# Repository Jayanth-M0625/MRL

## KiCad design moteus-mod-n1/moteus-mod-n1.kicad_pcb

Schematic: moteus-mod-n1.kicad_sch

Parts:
A1: PAD16AWG_TERM; 16AWG_TERMcustom
B1: PAD16AWG_TERM; 16AWG_TERMcustom
C1, C3, C6, C10, C33, C46, C47, C53, C64, C70, C72: 0.1uF; C0402; MPN MF-CAP-0402-0.1uF
C2: 0.47uF 100V; C0805; MPN 08051C474KAT2A
C4, C7: 0.1uF 100V; C0603; MPN GCJ188R72A104KA01D
C5, C8: 1uF; C0603; MPN C1608X7R1E105K080AE
C9: DNP; C0402
C11, C16, C21, C57: 1uF; C0402; MPN MF-CAP-0402-1uF
C12: 1uF 100V; C0805; MPN GCM21BC72A105KE36L
C13: 1uF; C0603; MPN MF-CAP-0603-1uF
C14, C17, C19: 0.1uF 100V; C1206; MPN 12061C104KAT2A
C15: 22uF; C1206; MPN GRM31CR71A226KE15L
C18: PAD16AWG_TERM; 16AWG_TERMcustom
C20: 22uF; C1206; MPN CL31B226KPHNNNE
C22, C23, C24, C25, C26, C27, C28, C29, C30, C31, C34, C35, C36, C37, C38, C39, C40, C41, C43, C44, C45, C48, C49, C50, C54, C55, C56, C58, C59, C60, C61, C62, C63, C65, C66, C67, C69, C71, C76, C77, C78, C79, C80, C81, C82, C83, C84, C85: 4.7uF 100V; C1206_NOBORDER; MPN GRJ31CC72A475KE01K
C32: 0.01uF; C0402; MPN MF-CAP-0402-0.01uF
C42, C51: 4.7uF 100V; C1206; MPN GRJ31CC72A475KE01K
C52: 4.7uF; C0603; MPN CL10A475KP8NNNC
C68: 10uF; C1206; MPN MF-CAP-1206-10uF
C73, C74, C75: 1000pF; C0402; MPN MF-CAP-0402-1nF
CAN1, CAN2, CAN3: 1X3
D1, D2, D3, D4, D5, D6, D7, D8, D9: BAT41KFILM; SODFL1608X70N; MPN BAT41KFILM
D10: MF-LED-0603-RED; LED0603
D11: MF-LED-0603-RED; LED0603; MPN MF-LED-0603-GREEN
D12: DIODE-DO214AA; DO214AA; MPN SMBJ51D-M3/I
D13, D14: PAD24AWG_PAD; 24AWG_PAD
DAC1: PAD24AWG_PAD; 24AWG_PAD
DG1: PAD24AWG_PAD; 24AWG_PAD
L1: SRN4018-220M; IND_BOURNS_SRN4018; MANUFACTURER_PART_NUMBER 74404042470
L2: 74479887222A; IND_1008_WE-PMI_WRE; MPN 74479887222A
M1, M2, M3: MOUNT; M2.5MOUNT
Q1, Q3, Q5: TPH1R204PL_VIAS; SOP_ADVANCE_8_VIAS; MPN TPH2R408QM,L1Q
Q2, Q4, Q6: TPH1R204PLSOP_ADVANCE_8; SOP_ADVANCE_8; MPN TPH2R408QM,L1Q
R1, R2: 2k; R0402; MPN MF-RES-0402-2K
R3, R8, R13: 0; R0402; MPN MF-RES-0402-0
R4, R17: DNP; R0402
R5: DNP; R0805
R6, R7, R10, R11, R12: 7.5; R0402; MPN RC0402FR-077R5L
R9: 7.5; R0805; MPN RC0805FR-077R5L
R14, R16: 100k 1%; R0402; MPN RC0402FR-07100KL
R15: 4.7k 1%; R0402; MPN RC0402FR-074K7L
R18, R21: 560; R0402; MPN MF-RES-0402-560
R19: 47k NTC; R0402; MPN NCP15WB473F03RC
R20, R22: 10k 1%; R0402; MPN RC0402FR-0710KL
R23, R24, R25: 22; R0402; MPN MF-RES-0402-22
RA1: 0.5mOhm 1% 2W; M1206; MPN HCS1206FTL500
RB1: 0.5mOhm 1% 2W; M1206; MPN HCS1206FTL500
RC1: 0.5mOhm 1% 2W; M1206; MPN HCS1206FTL500
SH1: SHORTMEDIUM; SHORT_TOP-MEDIUM
SH2, SH3, SH4: SHORTT5; SHORT_TOP-50
SWD1: JST-ZH6; JST_S6B-ZR-SM4A-TF(LF)(SN); MPN S6B-ZR-SM4A-TF(LF)(SN)
TEMP1: 1X2
U1: TCAN1042HGV; SOIC8; MPN TCAN1057AEVDRQ1
U2: AS5147; TSSOP14; MPN AS5047P-ATSM
U3: DRV8353S; WQFN-40; MPN DRV8353FSRTAR
U4: MAX15062AATA+T; 21-0487A_MXM; MANUFACTURER_PART_NUMBER MAX15062BATA+T
U5: ADP5301ACBZ-4-R7; BGA9C50P3X3_165X187X66; MPN ADP5301ACBZ-4-R7
U6: STM32G474CEU6; QFN50P700X700X60-49N; MPN STM32G474CEU6
VN1: PAD16AWG_TERM; 16AWG_TERMcustom
VP1: PAD16AWG_TERM; 16AWG_TERMcustom

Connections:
+3V3: C3.P$1, C6.P$2, C10.P$1, C20.P$1, C21.P$1, C46.P$1, C47.P$1, C52.P$1, C57.P$1, C64.P$1, C68.P$2, C70.P$1, D14.P$1, L2.1, R1.P$1, R2.P$1, R3.P$2, R16.P$2, R18.P$1, R19.P$1, R21.P$1, SWD1.6, TEMP1.1, U1.5 (VIO), U2.12 (VDD3V), U3.24 (VREF), U5.C2 (FB), U6.1 (VBAT), U6.20 (VREF+), U6.21 (VDDA), U6.23 (VDD_1), U6.35 (VDD_2), U6.48 (VDD_3)
+5V: C1.P$1, C15.P$1, C16.P$1, D13.P$1, L1.1, R13.P$2, U1.3 (VCC), U4.4 (FB/VOUT), U5.A2 (PVIN), U5.A3 (EN)
/AS5047_CS: U2.1 (CS/), U6.19 (PB2)
/AUX1_A: U2.2 (CLK), U6.13 (PA5), U6.27 (PB14)
/AUX1_B: U2.3 (MISO), U6.42 (PB4)
/AUX1_C: U2.4 (MOSI), U6.15 (PA7)
/CAN_N: CAN1.2, CAN2.2, CAN3.2, R5.P$2, U1.6 (CANL)
/CAN_P: CAN1.1, CAN2.1, CAN3.1, R5.P$1, U1.7 (CANH)
/CAN_RX: U1.4 (RXD), U6.43 (PB5)
/CAN_TX: U1.1 (TXD), U6.44 (PB6)
/CUR1: R23.P$1, U3.23 (SOA)
/CUR2: R24.P$1, U3.22 (SOB)
/CUR3: R25.P$1, U3.21 (SOC)
/DAC: DAC1.P$1, R16.P$1, R17.P$2, U6.12 (PA4)
/DRV8323_CS: U3.30 (CS), U6.17 (PB0)
/DRV8323_MISO: R1.P$2, U3.27 (MISO), U6.40 (PC11)
/DRV8323_MOSI: U3.28 (MOSI), U6.2 (PC13)
/DRV8323_SCLK: U3.29 (SCLK), U6.39 (PC10)
/FCUR1: C73.P$1, R23.P$2, U6.11 (PA3)
/FCUR2: C74.P$1, R24.P$2, U6.14 (PA6)
/FCUR3: C75.P$1, R25.P$2, U6.18 (PB1)
/GHA: D2.1 (K), R7.P$1, U3.6 (GHA)
/GHA_D: D2.2 (A), Q1.4 (G), R7.P$2
/GHB: D5.1 (K), R10.P$1, U3.15 (GHB)
/GHB_D: D5.2 (A), Q3.4 (G), R10.P$2
/GHC: D7.1 (K), R12.P$1, U3.16 (GHC)
/GHC_D: D7.2 (A), Q5.4 (G), R12.P$2
/GLA: D1.1 (K), R6.P$1, U3.8 (GLA)
/GLA_D: D1.2 (A), D3.1 (K), Q2.4 (G), R6.P$2
/GLB: D4.1 (K), R9.P$1, U3.13 (GLB)
/GLB_D: D4.2 (A), D6.1 (K), Q4.4 (G), R9.P$2
/GLC: D8.1 (K), R11.P$1, U3.18 (GLC)
/GLC_D: D8.2 (A), D9.1 (K), Q6.4 (G), R11.P$2
/LED1: D10.CATHODE, U6.28 (PB15)
/LED2: D11.CATHODE, U6.29 (PC6)
/MOTOR1: U3.32 (INHA), U6.8 (PA0)
/MOTOR2: U3.34 (INHB), U6.9 (PA1)
/MOTOR3: U3.36 (INHC), U6.10 (PA2)
/MOTOR_ENABLE: U3.31 (ENABLE), U6.3 (PC14-OSC32_IN)
/MOTOR_FAULT: R2.P$2, U3.26 (FAULT), U6.26 (PB13)
/MOTOR_HIZ: U3.33 (INLA), U3.35 (INLB), U3.37 (INLC), U6.4 (PC15-OSC32_OUT)
/NRST: C33.P$1, SWD1.2, U6.7 (PG10-NRST)
/SHA: A1.1, A1.2, A1.3, A1.4, A1.5, A1.6, A1.7, A1.8, A1.9, A1.10, A1.11, A1.12, A1.13, Q1.1 (S), Q1.2 (S), Q1.3 (S), Q2.5 (D), Q2.6 (D), Q2.7 (D), Q2.8 (D), Q2.PAD (D), U3.7 (SHA)
/SHB: B1.1, B1.2, B1.3, B1.4, B1.5, B1.6, B1.7, B1.8, B1.9, B1.10, B1.11, B1.12, B1.13, Q3.1 (S), Q3.2 (S), Q3.3 (S), Q4.5 (D), Q4.6 (D), Q4.7 (D), Q4.8 (D), Q4.PAD (D), U3.14 (SHB)
/SHC: C18.1, C18.2, C18.3, C18.4, C18.5, C18.6, C18.7, C18.8, C18.9, C18.10, C18.11, C18.12, C18.13, Q5.1 (S), Q5.2 (S), Q5.3 (S), Q6.5 (D), Q6.6 (D), Q6.7 (D), Q6.8 (D), Q6.PAD (D), U3.17 (SHC)
/SWCLK: SWD1.5, U6.37 (PA14)
/SWDIO: SWD1.3, U6.36 (PA13)
/SXA_N: SH2.1, U3.10 (SNA)
/SXA_P: C14.P$2, Q2.1 (S), Q2.2 (S), Q2.3 (S), RA1.2, U3.9 (SPA)
/SXB_N: SH3.1, U3.11 (SNB)
/SXB_P: C17.P$2, Q4.1 (S), Q4.2 (S), Q4.3 (S), RB1.2, U3.12 (SPB)
/SXC_N: SH4.1, U3.20 (SNC)
/SXC_P: C19.P$2, Q6.1 (S), Q6.2 (S), Q6.3 (S), RC1.2, U3.19 (SPC)
/VBAT_SENSE: C32.P$1, R14.P$1, R15.P$2, U6.31 (PA9)
/VSW: L1.2, U4.8 (LX)
/VTEMP_FET: C53.P$1, R19.P$2, R20.P$1, U6.25 (PB12)
/VTEMP_MOT: C72.P$1, R22.P$1, TEMP1.2, U6.30 (PA8)
unnamed: C9.P$1, M3.P$1, R4.P$1
unnamed: D10.ANODE, R18.P$2
unnamed: D11.ANODE, R21.P$2
unnamed: R3.P$1, U2.11 (VDD5V)
unnamed: C7.P$1, U3.2 (CPH)
unnamed: C7.P$2, U3.1 (CPL)
unnamed: C11.P$2, U3.38 (DVDD)
unnamed: C5.P$2, U3.5 (VCP)
unnamed: C8.P$2, U3.40 (VGLS)
unnamed: R8.P$2, U4.5 (MODE)
unnamed: C13.P$1, U4.3 (VCC)
unnamed: L2.2, U5.A1 (SW)
unnamed: R13.P$1, U5.B3 (SYNC/_MODE)
V+: C2.P$1, C4.P$1, C5.P$1, C12.P$1, C14.P$1, C17.P$1, C19.P$1, C22.P$1, C23.P$1, C24.P$1, C25.P$1, C26.P$1, C27.P$1, C28.P$1, C29.P$1, C30.P$1, C31.P$1, C34.P$1, C35.P$1, C36.P$1, C37.P$1, C38.P$1, C39.P$1, C40.P$1, C41.P$1, C42.P$1, C43.P$1, C44.P$1, C45.P$1, C48.P$1, C49.P$1, C50.P$1, C51.P$1, C54.P$1, C55.P$1, C56.P$1, C58.P$1, C59.P$1, C60.P$1, C61.P$1, C62.P$1, C63.P$1, C65.P$1, C66.P$1, C67.P$1, C69.P$1, C71.P$1, C76.P$1, C77.P$1, C78.P$1, C79.P$1, C80.P$1, C81.P$1, C82.P$1, C83.P$1, C84.P$1, C85.P$1, D12.C, Q1.5 (D), Q1.6 (D), Q1.7 (D), Q1.8 (D), Q1.PAD (D), Q3.5 (D), Q3.6 (D), Q3.7 (D), Q3.8 (D), Q3.PAD (D), Q5.5 (D), Q5.6 (D), Q5.7 (D), Q5.8 (D), Q5.PAD (D), R14.P$2, U3.3 (VM), U3.4 (VDRAIN), U4.1 (VIN), U4.2 (EN/UVLO), VP1.1, VP1.2, VP1.3, VP1.4, VP1.5, VP1.6, VP1.7, VP1.8, VP1.9, VP1.10, VP1.11, VP1.12, VP1.13

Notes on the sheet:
check component placement
POWER INPUT AND MOUNTING
CAN_L = CAN_N
OPTIONAL 120 TERMINATION RESISTOR
Need to connect either PA5 or PB14. Decide which one
BULK DC CAPS
MICROCONTROLLER
CAN_H = CAN_P
POWER STAGE
GATE DRIVER
Added 10 more DC Caps
NTC: Temperature sensing - keep near MOSFETs
Rotary encoder
This is where GND and V- are shorted
check how to connect this
CAN / ENCODER
check placement
This stage converts V+ into 5V and 3.3V
DEBUG
EXTERNAL CONNECTORS
PCB rev divider HI / LO r1.1/r1.2 - open / 100k r1.3 - 100k / open
REGULATORS
SENSE / LED

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
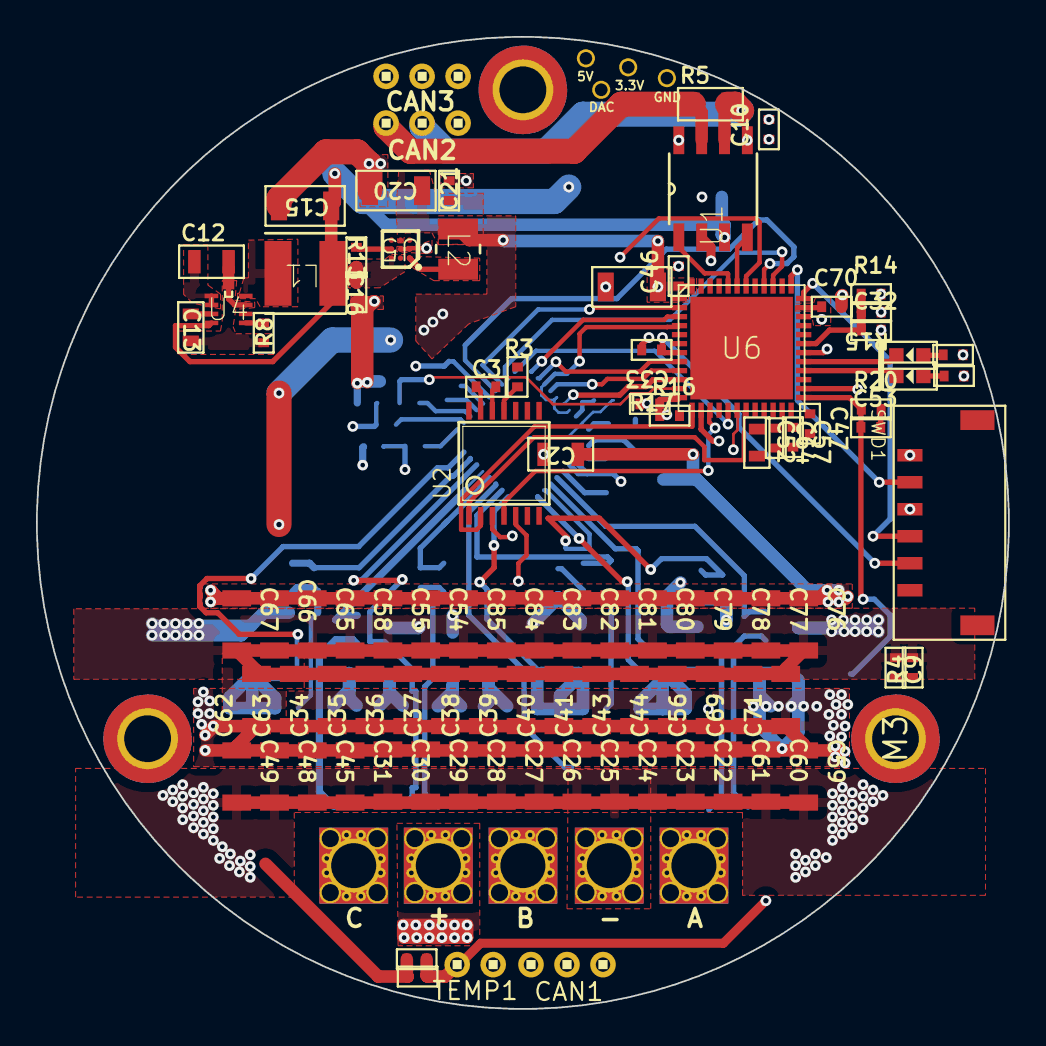
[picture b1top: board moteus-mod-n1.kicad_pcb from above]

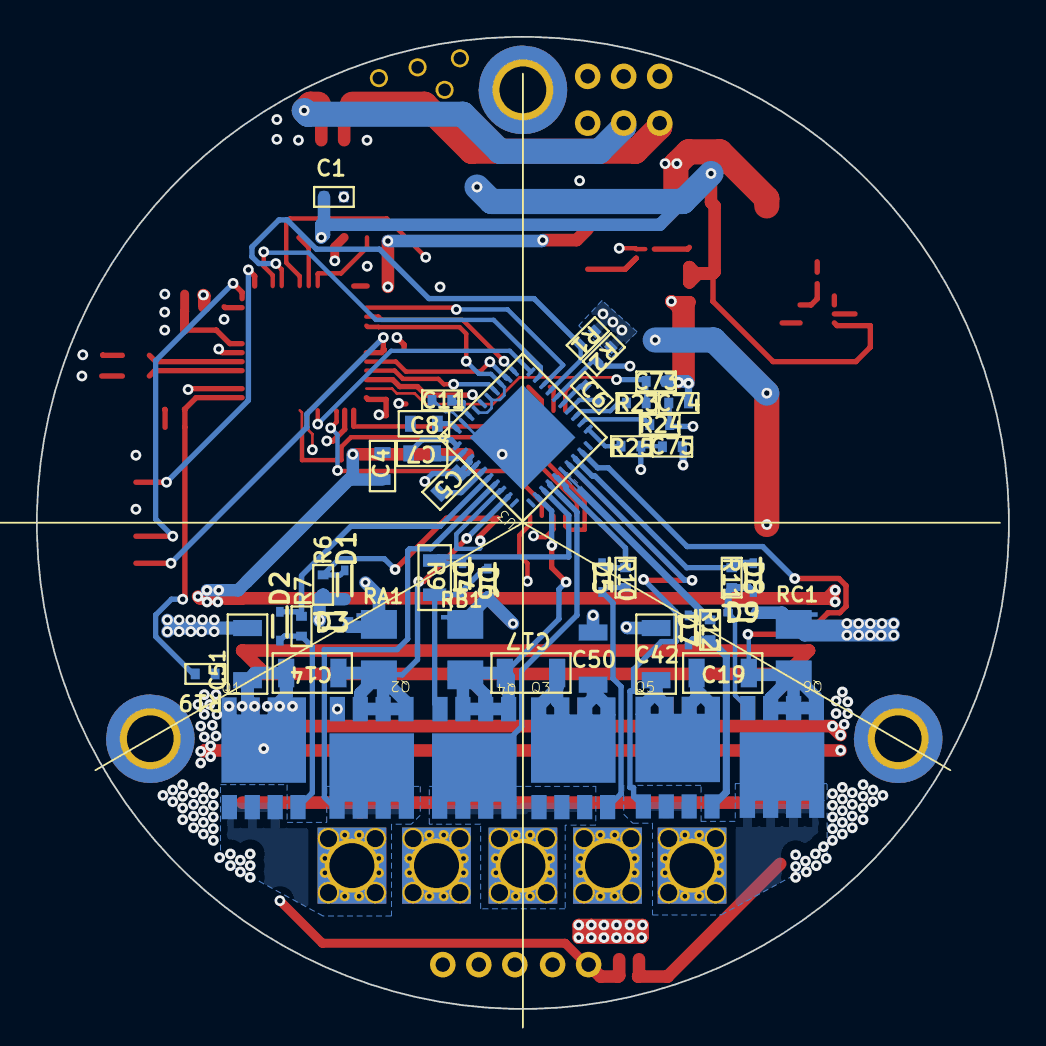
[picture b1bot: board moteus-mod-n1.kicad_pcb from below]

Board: 4 copper layers, 54.0 x 54.0 mm, 158 parts (50 on the bottom side), 73 nets.

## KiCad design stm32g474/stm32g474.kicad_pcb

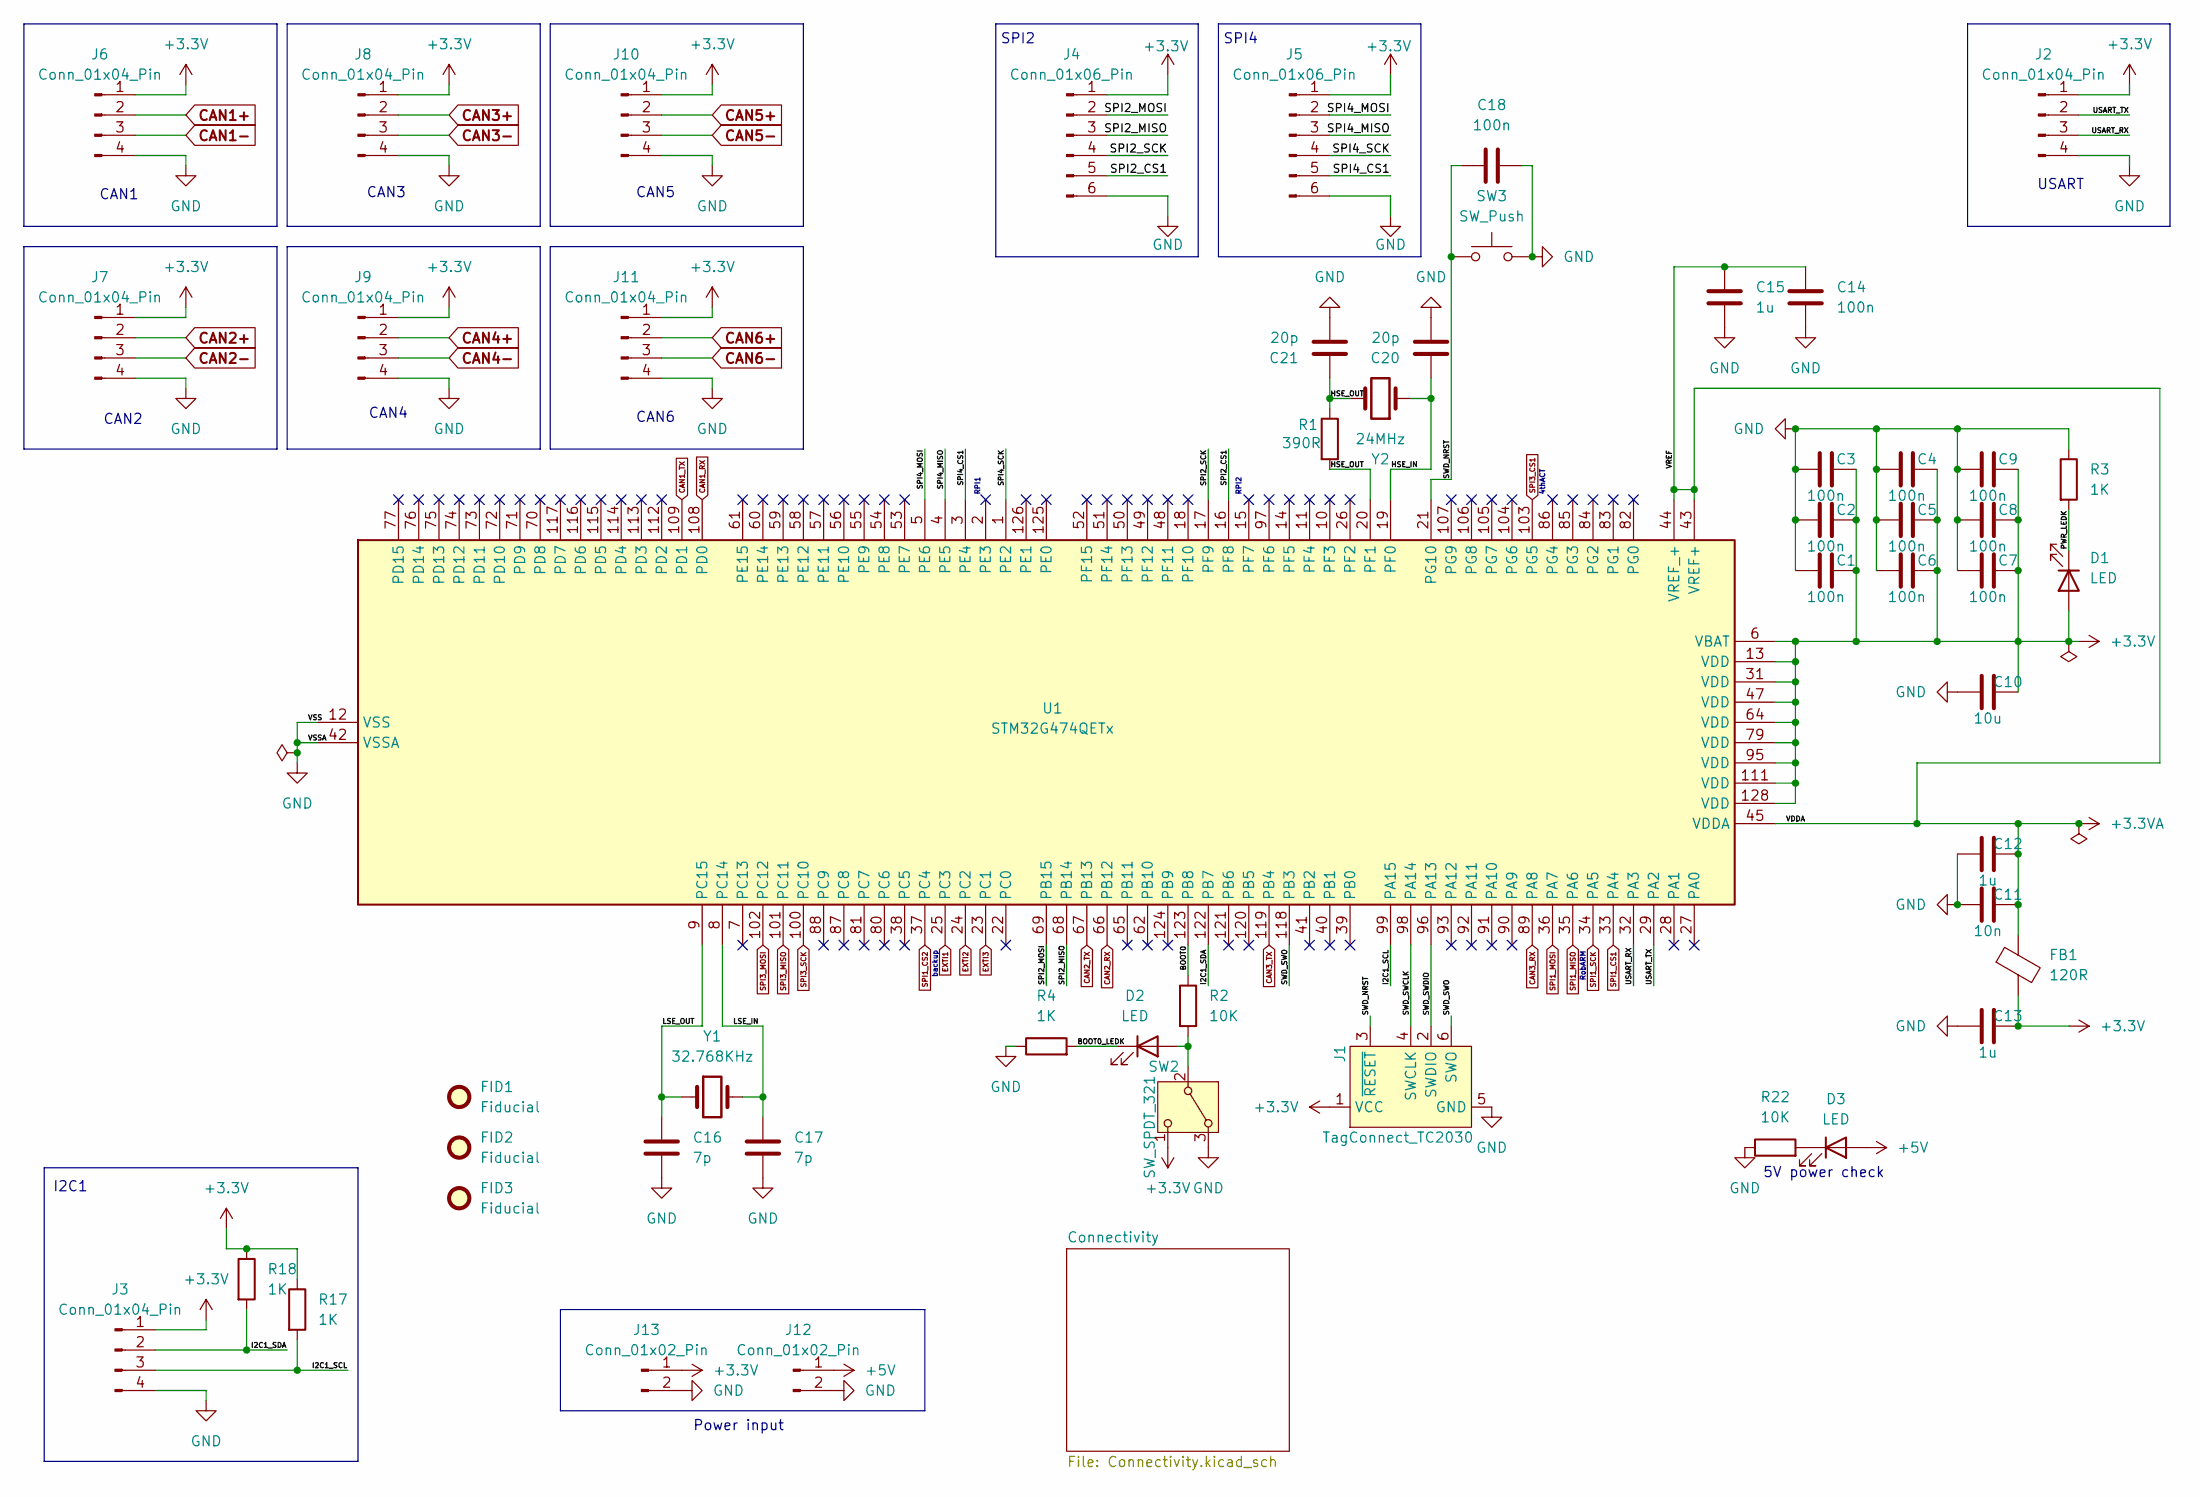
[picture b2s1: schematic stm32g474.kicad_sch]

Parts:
C1, C2, C3, C4, C5, C6, C7, C8, C9, C14, C18: 100n; C_0402_1005Metric; Manufacturer Part Number 0402ZC104MAT2A
C10: 10u; C_0805_2012Metric; Manufacturer Part Number C0805C106K8PAC
C11: 10n; C_0402_1005Metric
C12, C13, C15: 1u; C_0402_1005Metric
C16, C17: 7p; C_0402_1005Metric
C20, C21: 20p; C_0402_1005Metric
D1, D2, D3: LED; LED_0402_1005Metric
FB1: 120R; L_0603_1608Metric
FID1, FID2, FID3: Fiducial; Fiducial_0.5mm_Mask1.5mm
J1: TagConnect_TC2030; Tag-Connect_TC2030-IDC-FP_2x03_P1.27mm_Vertical
J2, J3, J6, J7, J8, J9, J10, J11: Conn_01x04_Pin; PinHeader_1x04_P2.54mm_Vertical
J4, J5: Conn_01x06_Pin; PinHeader_1x06_P2.54mm_Horizontal
J12, J13: Conn_01x02_Pin; PinHeader_1x02_P2.54mm_Vertical
R1: 390R; R_0402_1005Metric
R2, R22: 10K; R_0402_1005Metric
R3, R4, R17, R18: 1K; R_0402_1005Metric
SW2: SW_SPDT_321; SW_SPDT_PCM12
SW3: SW_Push; SW_SPST_CK_RS282G05A3
U1: STM32G474QETx; LQFP-128_14x14mm_P0.4mm
Y1: 32.768KHz; Crystal_SMD_3215-2Pin_3.2x1.5mm; Manufacturer Part Number CM7V-T1A-32.768kHz-7pF-10PPM-TA-QC T3
Y2: 24MHz; Crystal_SMD_TXC_7M-4Pin_3.2x2.5mm; Manufacturer Part Number ECS-240-20-33-CKM-TR3

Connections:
+3.3V: C1.1, C2.1, C3.1, C4.1, C5.1, C6.1, C7.1, C8.1, C9.1, C10.1, C13.1, D1.2 (A), FB1.2, J1.1 (VCC), J2.1, J3.1, J4.1, J5.1, J6.1, J7.1, J8.1, J9.1, J10.1, J11.1, J13.1, R17.1, R18.1, SW2.1 (C), U1.6 (VBAT), U1.13 (VDD), U1.31 (VDD), U1.47 (VDD), U1.64 (VDD), U1.79 (VDD), U1.95 (VDD), U1.111 (VDD), U1.128 (VDD); also elsewhere on the board
+3.3VA: C11.1, C12.1, C14.1, C15.1, FB1.1, U1.43 (VREF+), U1.44 (VREF_+), U1.45 (VDDA)
/BOOT0: R2.1, U1.123 (PB8)
/BOOT0_LEDK: D2.1 (K), R4.2
/HSE_IN: C20.1, U1.19 (PF0), Y2.1
/HSE_OUT: C21.1, R1.1, R1.2, U1.20 (PF1), Y2.2
/I2C1_SCL: J3.3, R17.2, U1.99 (PA15)
/I2C1_SDA: J3.2, R18.2, U1.122 (PB7)
/LSE_IN: C17.1, U1.8 (PC14), Y1.2
/LSE_OUT: C16.1, U1.9 (PC15), Y1.1
/PWR_LEDK: D1.1 (K), R3.2
/SPI2_CS1: J4.5, U1.16 (PF8)
/SPI2_MISO: J4.3, U1.68 (PB14)
/SPI2_MOSI: J4.2, U1.69 (PB15)
/SPI2_SCK: J4.4, U1.17 (PF9)
/SPI4_CS1: J5.5, U1.3 (PE4)
/SPI4_MISO: J5.3, U1.4 (PE5)
/SPI4_MOSI: J5.2, U1.5 (PE6)
/SPI4_SCK: J5.4, U1.1 (PE2)
/SWD_NRST: C18.2, J1.3 (~RESET), SW3.1, U1.21 (PG10)
/SWD_SWCLK: J1.4 (SWCLK), U1.98 (PA14)
/SWD_SWDIO: J1.2 (SWDIO), U1.96 (PA13)
/SWD_SWO: J1.6 (SWO), U1.118 (PB3)
/USART_RX: J2.3, U1.32 (PA3)
/USART_TX: J2.2, U1.29 (PA2)
CAN1+: J6.2; also elsewhere on the board
CAN1-: J6.3; also elsewhere on the board
CAN1_RX: U1.108 (PD0); also elsewhere on the board
CAN1_TX: U1.109 (PD1); also elsewhere on the board
CAN2+: J7.2; also elsewhere on the board
CAN2-: J7.3; also elsewhere on the board
CAN2_RX: U1.66 (PB12); also elsewhere on the board
CAN2_TX: U1.67 (PB13); also elsewhere on the board
CAN3+: J8.2; also elsewhere on the board
CAN3-: J8.3; also elsewhere on the board
CAN3_RX: U1.89 (PA8); also elsewhere on the board
CAN3_TX: U1.119 (PB4); also elsewhere on the board
CAN4+: J9.2; also elsewhere on the board
CAN4-: J9.3; also elsewhere on the board
CAN5+: J10.2; also elsewhere on the board
CAN5-: J10.3; also elsewhere on the board
CAN6+: J11.2; also elsewhere on the board
CAN6-: J11.3; also elsewhere on the board
EXTI1: U1.25 (PC3); also elsewhere on the board
EXTI2: U1.24 (PC2); also elsewhere on the board
EXTI3: U1.23 (PC1); also elsewhere on the board
GND: C1.2, C2.2, C3.2, C4.2, C5.2, C6.2, C7.2, C8.2, C9.2, C10.2, C11.2, C12.2, C13.2, C14.2, C15.2, C16.2, C17.2, C18.1, C20.2, C21.2, J1.5 (GND), J2.4, J3.4, J4.6, J5.6, J6.4, J7.4, J8.4, J9.4, J10.4, J11.4, J12.2, J13.2, R3.1, R4.1, R22.1, SW2.3 (A), SW3.2, U1.12 (VSS), U1.30 (VSS), U1.42 (VSSA), U1.46 (VSS), U1.63 (VSS), U1.78 (VSS), U1.94 (VSS), U1.110 (VSS), U1.127 (VSS); also elsewhere on the board
unnamed: D2.2 (A), R2.2, SW2.2 (B)
SPI1_CS1: U1.33 (PA4); also elsewhere on the board
SPI1_CS2: U1.37 (PC4); also elsewhere on the board
SPI1_MISO: U1.35 (PA6); also elsewhere on the board
SPI1_MOSI: U1.36 (PA7); also elsewhere on the board
SPI1_SCK: U1.34 (PA5); also elsewhere on the board
SPI3_CS1: U1.103 (PG5); also elsewhere on the board
SPI3_MISO: U1.101 (PC11); also elsewhere on the board
SPI3_MOSI: U1.102 (PC12); also elsewhere on the board
SPI3_SCK: U1.100 (PC10); also elsewhere on the board

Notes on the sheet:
SPI2
CAN2
RobARM
USART
CAN1
5V power check
RPI1
backup
CAN6
SPI4
4thACT
CAN5
Power input
CAN3
I2C1
RPI2
CAN4

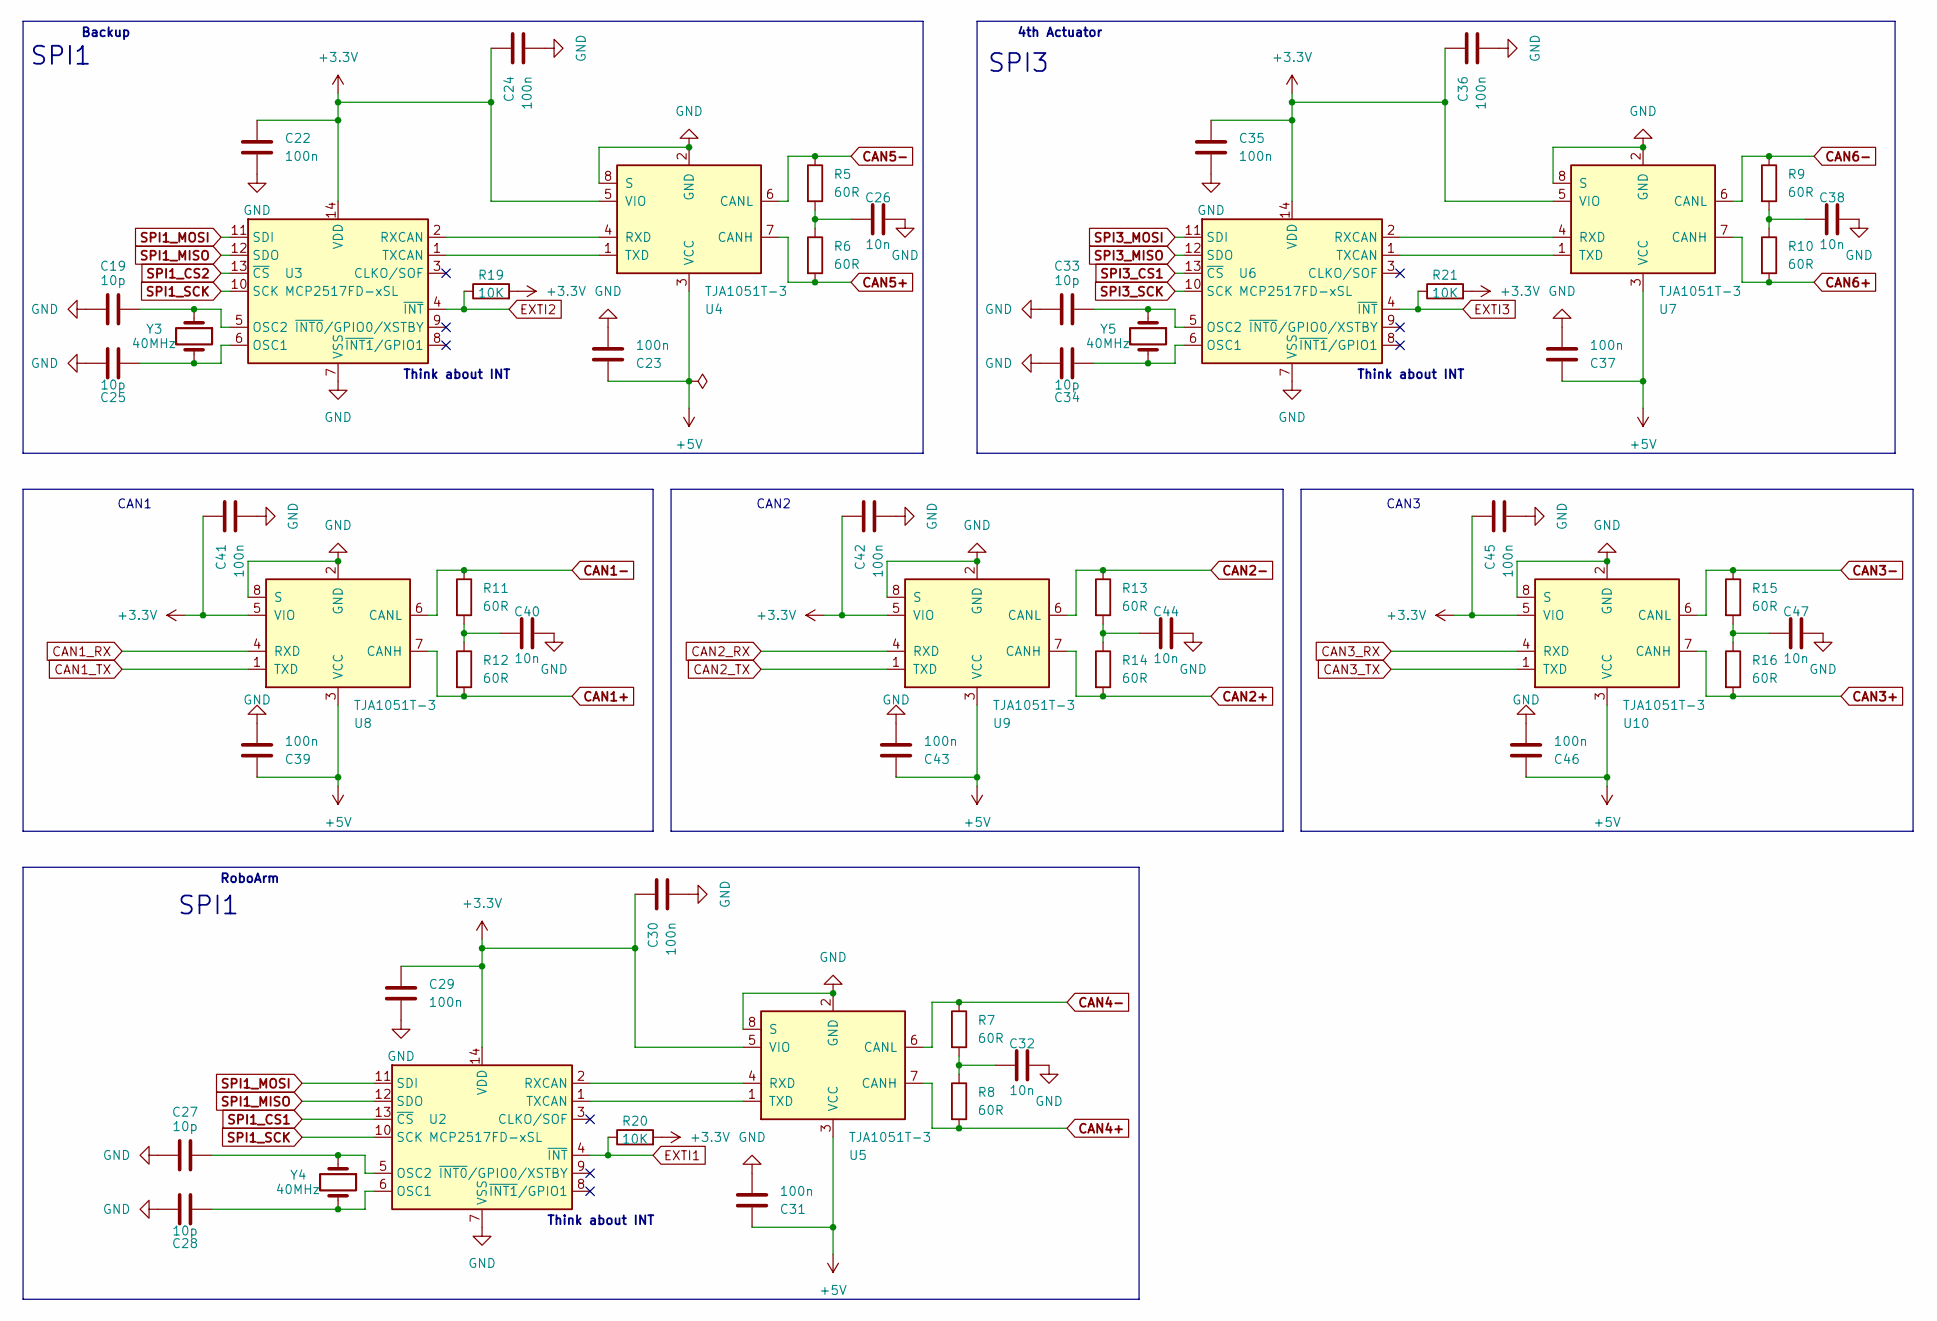
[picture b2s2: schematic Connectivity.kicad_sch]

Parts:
C19, C25, C27, C28, C33, C34: 10p; C_0402_1005Metric
C22, C23, C24, C29, C30, C31, C35, C36, C37, C39, C41, C42, C43, C45, C46: 100n; C_0402_1005Metric; Manufacturer Part Number 0402ZC104MAT2A
C26, C32, C38, C40, C44, C47: 10n; C_0402_1005Metric
R5, R6, R7, R8, R9, R10, R11, R12, R13, R14, R15, R16: 60R; R_0402_1005Metric
R19, R20, R21: 10K; R_0402_1005Metric
U2, U3, U6: MCP2517FD-xSL; SOIC-14_3.9x8.7mm_P1.27mm
U4, U5, U7, U8, U9, U10: TJA1051T-3; SOIC-8_3.9x4.9mm_P1.27mm
Y3, Y4, Y5: 40MHz; Crystal_SMD_TXC_7M-4Pin_3.2x2.5mm; Manufacturer Part Number CX3225FB40000F0FZZH1

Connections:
+3.3V: C22.1, C24.1, C29.1, C30.1, C35.1, C36.1, C41.1, C42.1, C45.1, R19.2, R20.2, R21.2, U2.14 (VDD), U3.14 (VDD), U4.5 (VIO), U5.5 (VIO), U6.14 (VDD), U7.5 (VIO), U8.5 (VIO), U9.5 (VIO), U10.5 (VIO); also elsewhere on the board
CAN1+: R12.2, U8.7 (CANH); also elsewhere on the board
CAN1-: R11.1, U8.6 (CANL); also elsewhere on the board
CAN1_RX: U8.4 (RXD); also elsewhere on the board
CAN1_TX: U8.1 (TXD); also elsewhere on the board
CAN2+: R14.2, U9.7 (CANH); also elsewhere on the board
CAN2-: R13.1, U9.6 (CANL); also elsewhere on the board
CAN2_RX: U9.4 (RXD); also elsewhere on the board
CAN2_TX: U9.1 (TXD); also elsewhere on the board
CAN3+: R16.2, U10.7 (CANH); also elsewhere on the board
CAN3-: R15.1, U10.6 (CANL); also elsewhere on the board
CAN3_RX: U10.4 (RXD); also elsewhere on the board
CAN3_TX: U10.1 (TXD); also elsewhere on the board
CAN4+: R8.2, U5.7 (CANH); also elsewhere on the board
CAN4-: R7.1, U5.6 (CANL); also elsewhere on the board
CAN5+: R6.2, U4.7 (CANH); also elsewhere on the board
CAN5-: R5.1, U4.6 (CANL); also elsewhere on the board
CAN6+: R10.2, U7.7 (CANH); also elsewhere on the board
CAN6-: R9.1, U7.6 (CANL); also elsewhere on the board
EXTI1: R20.1, U2.4 (~INT); also elsewhere on the board
EXTI2: R19.1, U3.4 (~INT); also elsewhere on the board
EXTI3: R21.1, U6.4 (~INT); also elsewhere on the board
GND: C19.1, C22.2, C23.2, C24.2, C25.1, C26.2, C27.1, C28.1, C29.2, C30.2, C31.2, C32.2, C33.1, C34.1, C35.2, C36.2, C37.2, C38.2, C39.2, C40.2, C41.2, C42.2, C43.2, C44.2, C45.2, C46.2, C47.2, U2.7 (VSS), U3.7 (VSS), U4.2 (GND), U4.8 (S), U5.2 (GND), U5.8 (S), U6.7 (VSS), U7.2 (GND), U7.8 (S), U8.2 (GND), U8.8 (S), U9.2 (GND), U9.8 (S), U10.2 (GND), U10.8 (S); also elsewhere on the board
unnamed: C26.1, R5.2, R6.1
unnamed: C32.1, R7.2, R8.1
unnamed: C38.1, R9.2, R10.1
unnamed: C40.1, R11.2, R12.1
unnamed: C44.1, R13.2, R14.1
unnamed: C47.1, R15.2, R16.1
unnamed: C28.2, U2.6 (OSC1), Y4.2
unnamed: C27.2, U2.5 (OSC2), Y4.1
unnamed: U2.2 (RXCAN), U5.4 (RXD)
unnamed: U2.1 (TXCAN), U5.1 (TXD)
unnamed: C25.2, U3.6 (OSC1), Y3.2
unnamed: C19.2, U3.5 (OSC2), Y3.1
unnamed: U3.2 (RXCAN), U4.4 (RXD)
unnamed: U3.1 (TXCAN), U4.1 (TXD)
unnamed: C34.2, U6.6 (OSC1), Y5.2
unnamed: C33.2, U6.5 (OSC2), Y5.1
unnamed: U6.2 (RXCAN), U7.4 (RXD)
unnamed: U6.1 (TXCAN), U7.1 (TXD)
SPI1_CS1: U2.13 (~CS); also elsewhere on the board
SPI1_CS2: U3.13 (~CS); also elsewhere on the board
SPI1_MISO: U2.12 (SDO), U3.12 (SDO); also elsewhere on the board
SPI1_MOSI: U2.11 (SDI), U3.11 (SDI); also elsewhere on the board
SPI1_SCK: U2.10 (SCK), U3.10 (SCK); also elsewhere on the board
SPI3_CS1: U6.13 (~CS); also elsewhere on the board
SPI3_MISO: U6.12 (SDO); also elsewhere on the board
SPI3_MOSI: U6.11 (SDI); also elsewhere on the board
SPI3_SCK: U6.10 (SCK); also elsewhere on the board

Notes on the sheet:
SPI1
Think about INT
Backup
SPI3
4th Actuator
CAN3
RoboArm
CAN1
CAN2

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
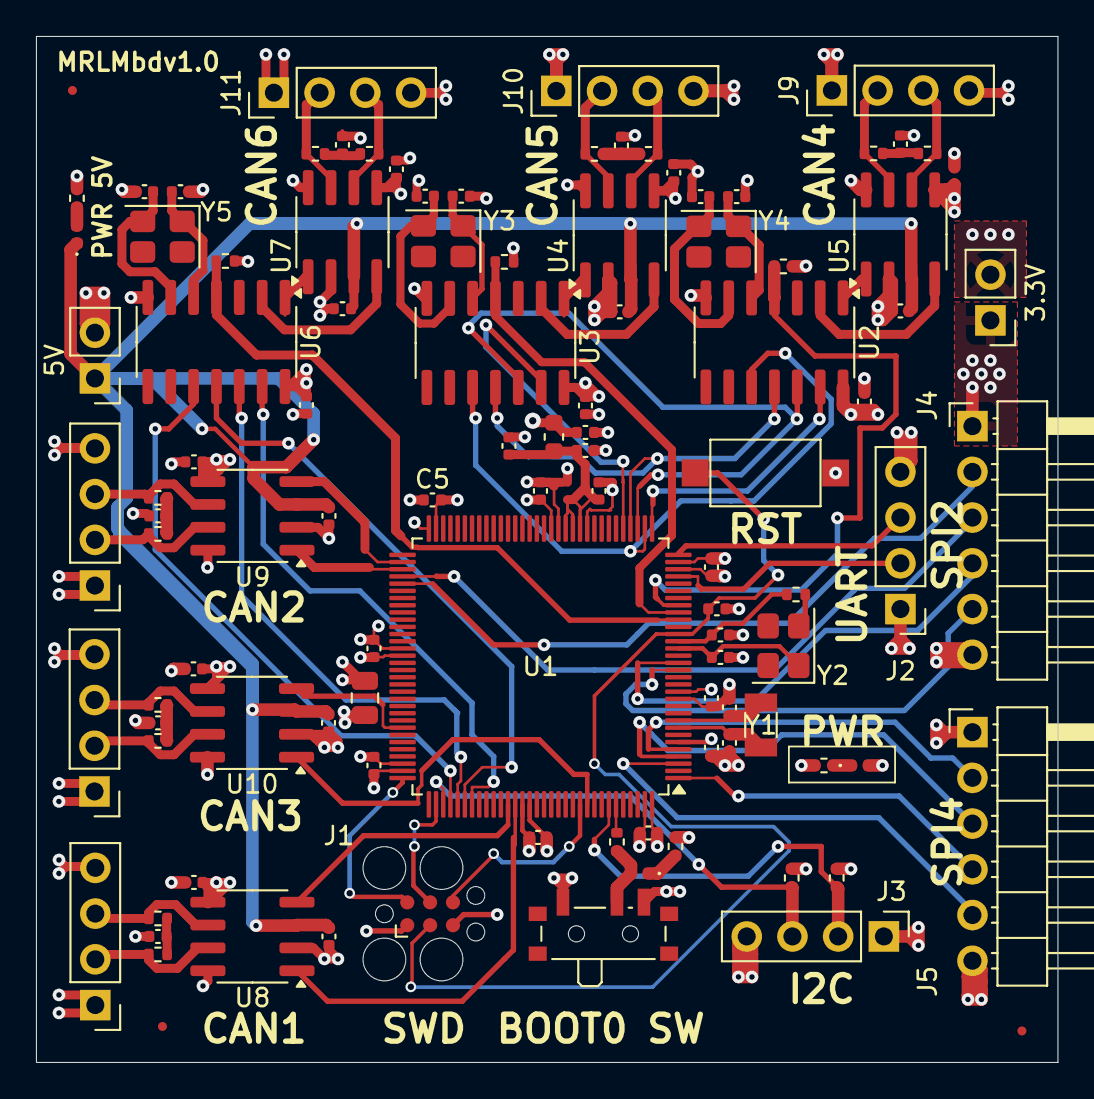
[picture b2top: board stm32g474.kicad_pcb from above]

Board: 4 copper layers, 56.8 x 57.0 mm, 104 parts (0 on the bottom side), 77 nets.

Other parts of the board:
3.3V, 5V: Conn_01x02_Pin; PinHeader_1x02_P2.54mm_Vertical

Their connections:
+3.3V: 3.3V.1; also elsewhere on the board
GND: 3.3V.2, 5V.2; also elsewhere on the board

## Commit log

2025-09-26 Added schematic
2025-10-05 pcb update
